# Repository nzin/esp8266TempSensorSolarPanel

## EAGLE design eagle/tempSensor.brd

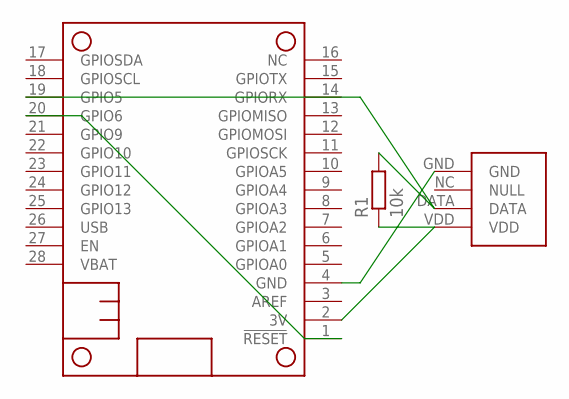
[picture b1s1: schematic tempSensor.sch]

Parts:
MS1: FEATHERWING_NODIM; FEATHERWING_DIM
R1: 10k; 0207/10
U$1: DHT22

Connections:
3V: MS1.2 (3V), R1.1, U$1.VDD
unnamed: MS1.1 (!RESET), MS1.20 (GPIO6)
unnamed: MS1.4 (GND), U$1.GND
unnamed: MS1.19 (GPIO5), R1.2, U$1.DATA

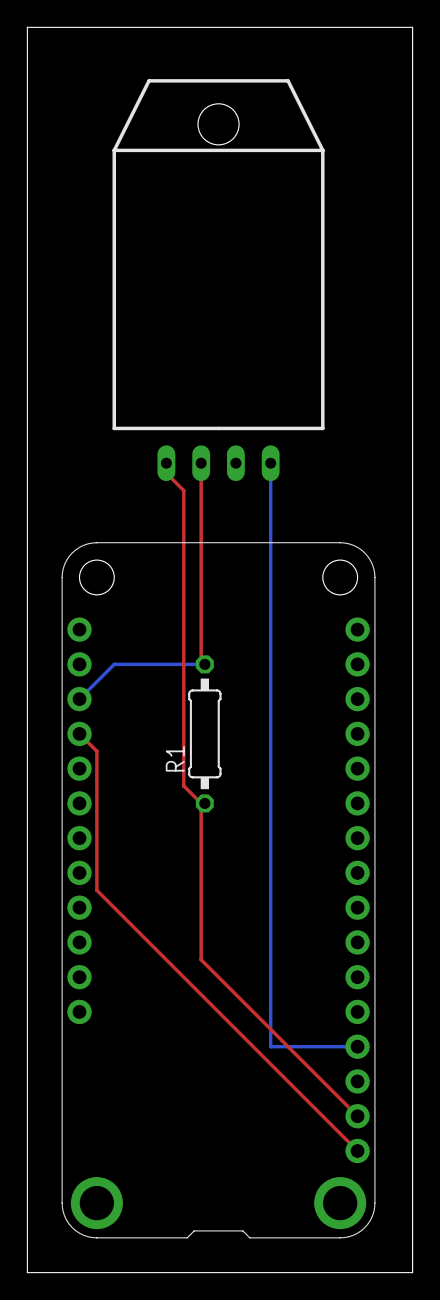
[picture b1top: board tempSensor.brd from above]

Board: 2 copper layers, 28.1 x 91.0 mm, 3 parts (0 on the bottom side), 4 nets.

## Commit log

2017-08-27 temp sensor code
2017-08-27 Eagle schema
2017-08-27 box drawing
